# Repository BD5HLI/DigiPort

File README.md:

# 简介

面向八重洲FT-891的FT8模式集成接口，内置一个2口的USB2.0 HUB和一个USB声卡，通过一个Type-C接口连接电脑或者手机，解决FT-891没有内置声卡的问题。

本项目采用了Digirig-Mobile项目（https://github.com/softcomplex/Digirig-Mobile ）的符号库、封装库和3D器件模型，参考了Digirig DR-891的原理图（https://digirig.net/digirig-dr-891-setup-manual/ ）设计，精简了几乎用不到的CM108B GPIO脚的PTT功能，保留了VOX-PTT功能。此外，本项目的被动器件（电阻、电容）均采用0402手焊封装，便于手工焊接。

本项目虽然面向FT-891设计，实际上可以仅使用USB声卡的功能，从而适用于绝大多数带有音频输入输出接口的电台，比如K5、K6手台，配合相应的软件可以实现SSTV、APRS等玩法。

# 电路板渲染图

电路板正面：

电路板反面：

# 接口

DigiPort在电脑侧的接口为type c接口，可使用c to a或c to c数据线连接电脑或者手机；在电台侧的接口包括两个3.5mm的4芯TRRS接口，面向电路板器件面、type c接口在右侧时，左上的TRRS接口为音频/PTT接口，左下的TRRS接口为USB接口。

DigiPort的音频/PTT接口定义如下：  

```
   /\  
  |  |---------> 尖端   RIG_AFOUT 电台音频输出，接FT-891 DATA口的DATA OUT脚  
  |--|  
  |  |---------> 第一环 RIG_AFIN  电台音频输入，接FT-891 DATA口的DATA IN脚  
  |--|  
  |  |---------> 第二环 VOX_PTT   声控PTT，接FT-891 DATA口的PTT脚  
  |--|  
  |  |---------> 底部   GND       信号地，接FT-891 DATA口的GND脚  
__|  |__
|      |  
```

VOX_PTT信号用于没有USB串口的设备控制收发转换，控制源来自CM108B声卡的右声道，推荐采用1kHz或2kHz的单音作为VOX触发信号。

FT-891的DATA**插座**定义如下：

```
    /-----\      1脚：DATA IN  
   / 6 _ 5 \     2脚：GND  
  |4  |_|  3|    3脚：PTT  
   \ 2   1 /     4脚：SHIFT  
    \-----/      5脚：DATA OUT   
                 6脚：SQL   
```

DigiPort的电台侧USB接口定义如下：  

```
   /\  
  |  |---------> 尖端   +5V 电台USB口的+5V电源脚  
  |--|  
  |  |---------> 第一环 D-  电台USB口的D-脚  
  |--|  
  |  |---------> 第二环 D+  电台USB口的D+脚  
  |--|  
  |  |---------> 底部   GND 电台USB口的GND脚  
__|  |__  
|      |  
```

USB Type-B**插头**定义如下：

```
   /-+=+--+=+-\     1脚：+5V     
  /  |=|  |=|  \        
  |   1    2   |    2脚：D-  
  |            |   
  |   4    3   |    3脚：D+  
  |  |=|  |=|  |   
  |--+=+--+=+--|    4脚：GND  
```

# 各目录内容说明

- digiport-891目录下是kicad格式的原理图和PCB图。  
- endboard目录下是采用25mm * 25mm * 40mm对扣小铝壳的端板3D图纸。  
- 3D-models目录下是部分器件的3D模型，来自Digirig-Mobile项目。  
- footprints.pretty目录下是部分器件的封装库，来自Digirig-Mobile项目。  
- symbols目录下是部分器件的符号库，来自Digirig-Mobile项目。  

# 致谢

- 感谢LX6FB提供原版DR-891的照片。

- 感谢BG5ARO对端板设计提出了宝贵建议，并提供了CNC加工。

- 感谢BG5BQB提供了3D打印工艺的端板原型样件。

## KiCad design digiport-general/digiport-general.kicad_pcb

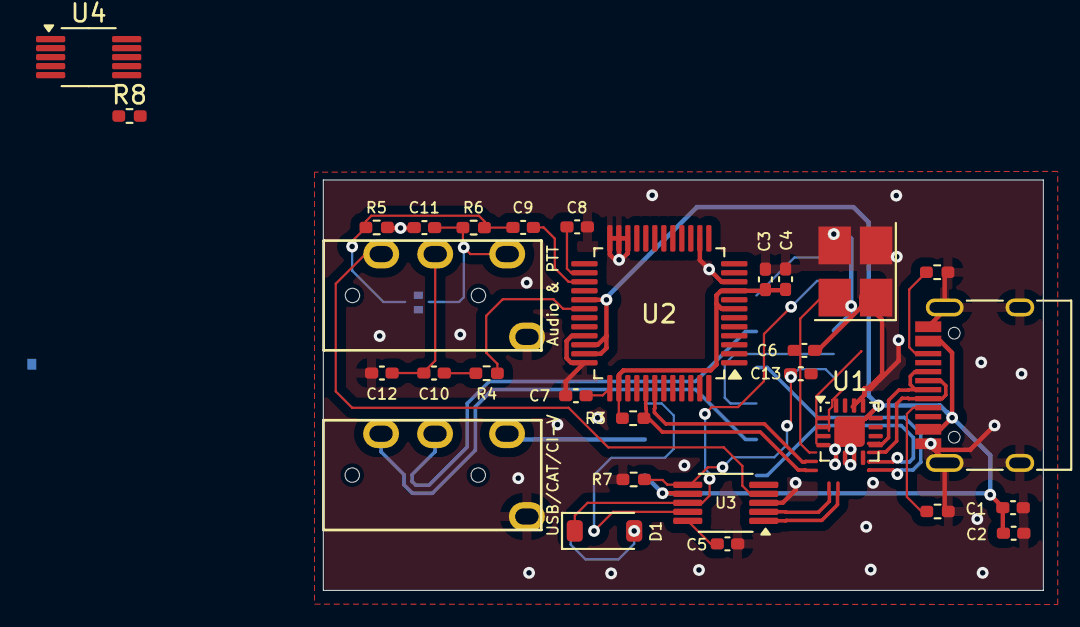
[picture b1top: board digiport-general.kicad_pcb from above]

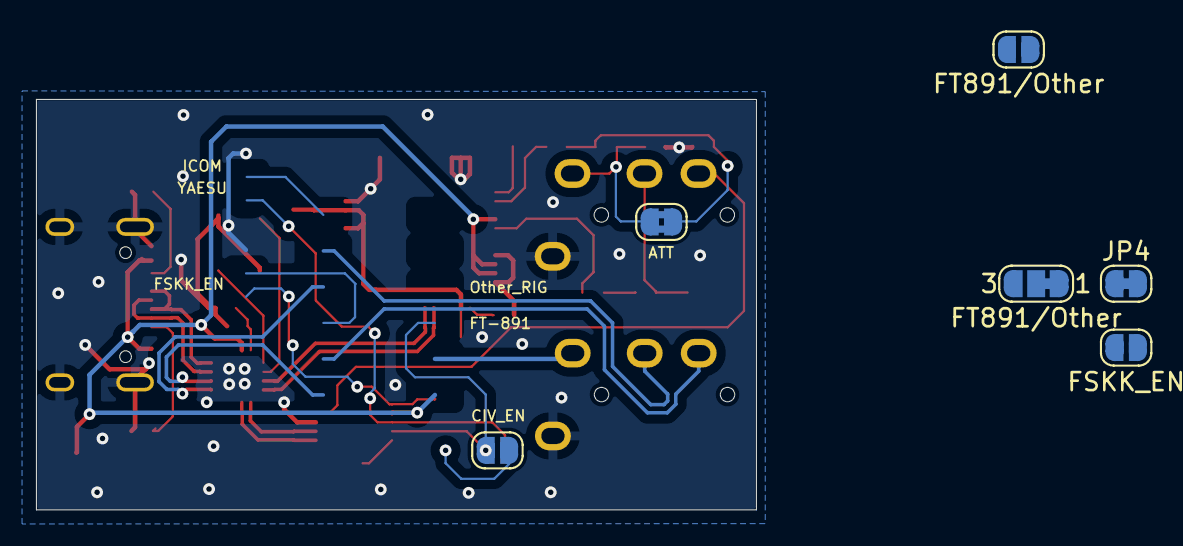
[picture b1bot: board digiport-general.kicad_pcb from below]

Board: 2 copper layers, 40.0 x 22.8 mm, 36 parts (2 on the bottom side), 35 nets.

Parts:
C1, C3, C6, C7, C8, C9, C10: 10uF; C_0402_1005Metric_Pad0.74x0.62mm_HandSolder
C2, C4, C5, C13: 100nF; C_0402_1005Metric_Pad0.74x0.62mm_HandSolder
C11, C12: 1nF; C_0402_1005Metric_Pad0.74x0.62mm_HandSolder
D1: 1N4148W; D_SOD-123
J1: Audio&PTT; TRRS-PJ-320A
J2: USB/CIV/CAT; TRRS-PJ-320A
J3: USB_C_Receptacle_USB2.0_16P; USB_C_Receptacle_HRO_TYPE-C-31-M-12
JP1: FT891/Other; SolderJumper2-BCu
JP2: FT891/Other; SolderJumper3-BCu
JP3: CIV_EN; SolderJumper-2_P1.3mm_Open_RoundedPad1.0x1.5mm
JP4: Yaesu/ICOM; SolderJumper-BCu-Bridged
JP5: FSKK_EN; SolderJumper2-BCu
JP6: ATT; SolderJumper-2_P1.3mm_Bridged2Bar_RoundedPad1.0x1.5mm
R1, R2: 5.1k; R_0402_1005Metric_Pad0.72x0.64mm_HandSolder
R3: 1.5k; R_0402_1005Metric_Pad0.72x0.64mm_HandSolder
R4: 22; R_0402_1005Metric_Pad0.72x0.64mm_HandSolder
R5, R8: 10k; R_0402_1005Metric_Pad0.72x0.64mm_HandSolder
R6: 100k; R_0402_1005Metric_Pad0.72x0.64mm_HandSolder
R7: 4.7k; R_0402_1005Metric_Pad0.72x0.64mm_HandSolder
U1: CH334P; QFN-16-1EP_3x3mm_P0.5mm_EP1.7x1.7mm_ThermalVias
U2: CM108B; LQFP-48_7x7mm_P0.5mm
U3: CH340X; MSOP-10_3x3mm_P0.5mm
U4: CH442E; MSOP-10_3x3mm_P0.5mm
Y1: 12MHz; Crystal_SMD_3225-4Pin_3.2x2.5mm_HandSoldering

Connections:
891USB_D+: U1.6 (DP3+), U4.7 (S2C)
891USB_D-: U1.5 (DM3-), U4.3 (S2B)
+3.3V: C3.1, C4.1, R3.1, U2.7 (PWRSEL), U2.9 (DREG33), U2.38 (MSEL)
+5V: C1.1, C2.1, J3.A4 (VBUS), J3.A9 (VBUS), J3.B4 (VBUS), J3.B9 (VBUS), JP2.1 (A), R8.1, U1.15 (V5), U2.29 (AVDD), U2.34 (AVDD), U2.35 (DVDD), U3.7 (VCC), U4.10 (VCC)
/DU+: J3.A6 (D+), J3.B6 (D+), U1.12 (DPU+)
/DU-: J3.A7 (D-), J3.B7 (D-), U1.11 (DMU-)
/RIG_AFIN: C10.1, C12.1, J1.R1
/RIG_AUOUT: C11.1, J1.T, JP6.2 (B), R6.2
AUDIO_D+: R3.2, U1.4 (DP4+), U2.41 (USBDP)
AUDIO_D-: U1.3 (DM4-), U2.42 (USBDM)
GND: C1.2, C2.2, C3.2, C4.2, C5.2, C6.1, C7.2, C8.1, C11.2, C12.2, C13.1, J1.S, J2.S, J3.A1 (GND), J3.A12 (GND), J3.B1 (GND), J3.B12 (GND), J3.S1 (SHIELD), JP1.1 (A), R1.2, R2.2, R5.1, R7.2, U1.17 (GND), U2.10 (MODE), U2.14 (DVSS), U2.22 (ADSEL), U2.23 (TEST), U2.24 (AVSS), U2.33 (AVSS), U2.36 (DVSS), U3.3 (GND), U4.5 (GND), U4.9 (EN#), Y1.2, Y1.4
unnamed: C10.2, R4.2
unnamed: D1.2 (A), JP3.2 (B)
unnamed: J3.A5 (CC1), R2.1
unnamed: J3.B5 (CC2), R1.1
unnamed: JP1.2 (B), R8.2, U4.1 (IN)
unnamed: C9.1, JP6.1 (A), R5.2, R6.1
unnamed: C6.2, C13.2, U1.16 (VDD33)
unnamed: U1.2 (XI), Y1.3
unnamed: U1.1 (XO), Y1.1
unnamed: C7.1, U2.37 (AREG36)
unnamed: R4.1, U2.30 (LOL)
unnamed: C9.2, U2.27 (MICIN)
unnamed: C8.2, U2.26 (VREF)
unnamed: C5.1, U3.10 (V3)
PC_DTR: JP5.1 (A), R7.1, U3.6 (TNOW/~DTR)
PC_RTS: J1.R2, U3.4 (~RTS)
PC_RxD: JP2.3 (B), JP3.1 (A), U3.9 (RXD)
PC_TxD: D1.1 (K), JP4.1 (A), U3.8 (TXD)
RIGD_R+: J2.R2, U4.6 (DC)
RIGD_R-: J2.R1, U4.4 (DB)
RIGD_T: J2.T, JP2.2 (C)
RIG_RX: JP4.2 (B), U4.2 (S1B)
SERIAL_D+: U1.8 (DP2+), U3.1 (UD+)
SERIAL_D-: U1.7 (DM2-), U3.2 (UD-)

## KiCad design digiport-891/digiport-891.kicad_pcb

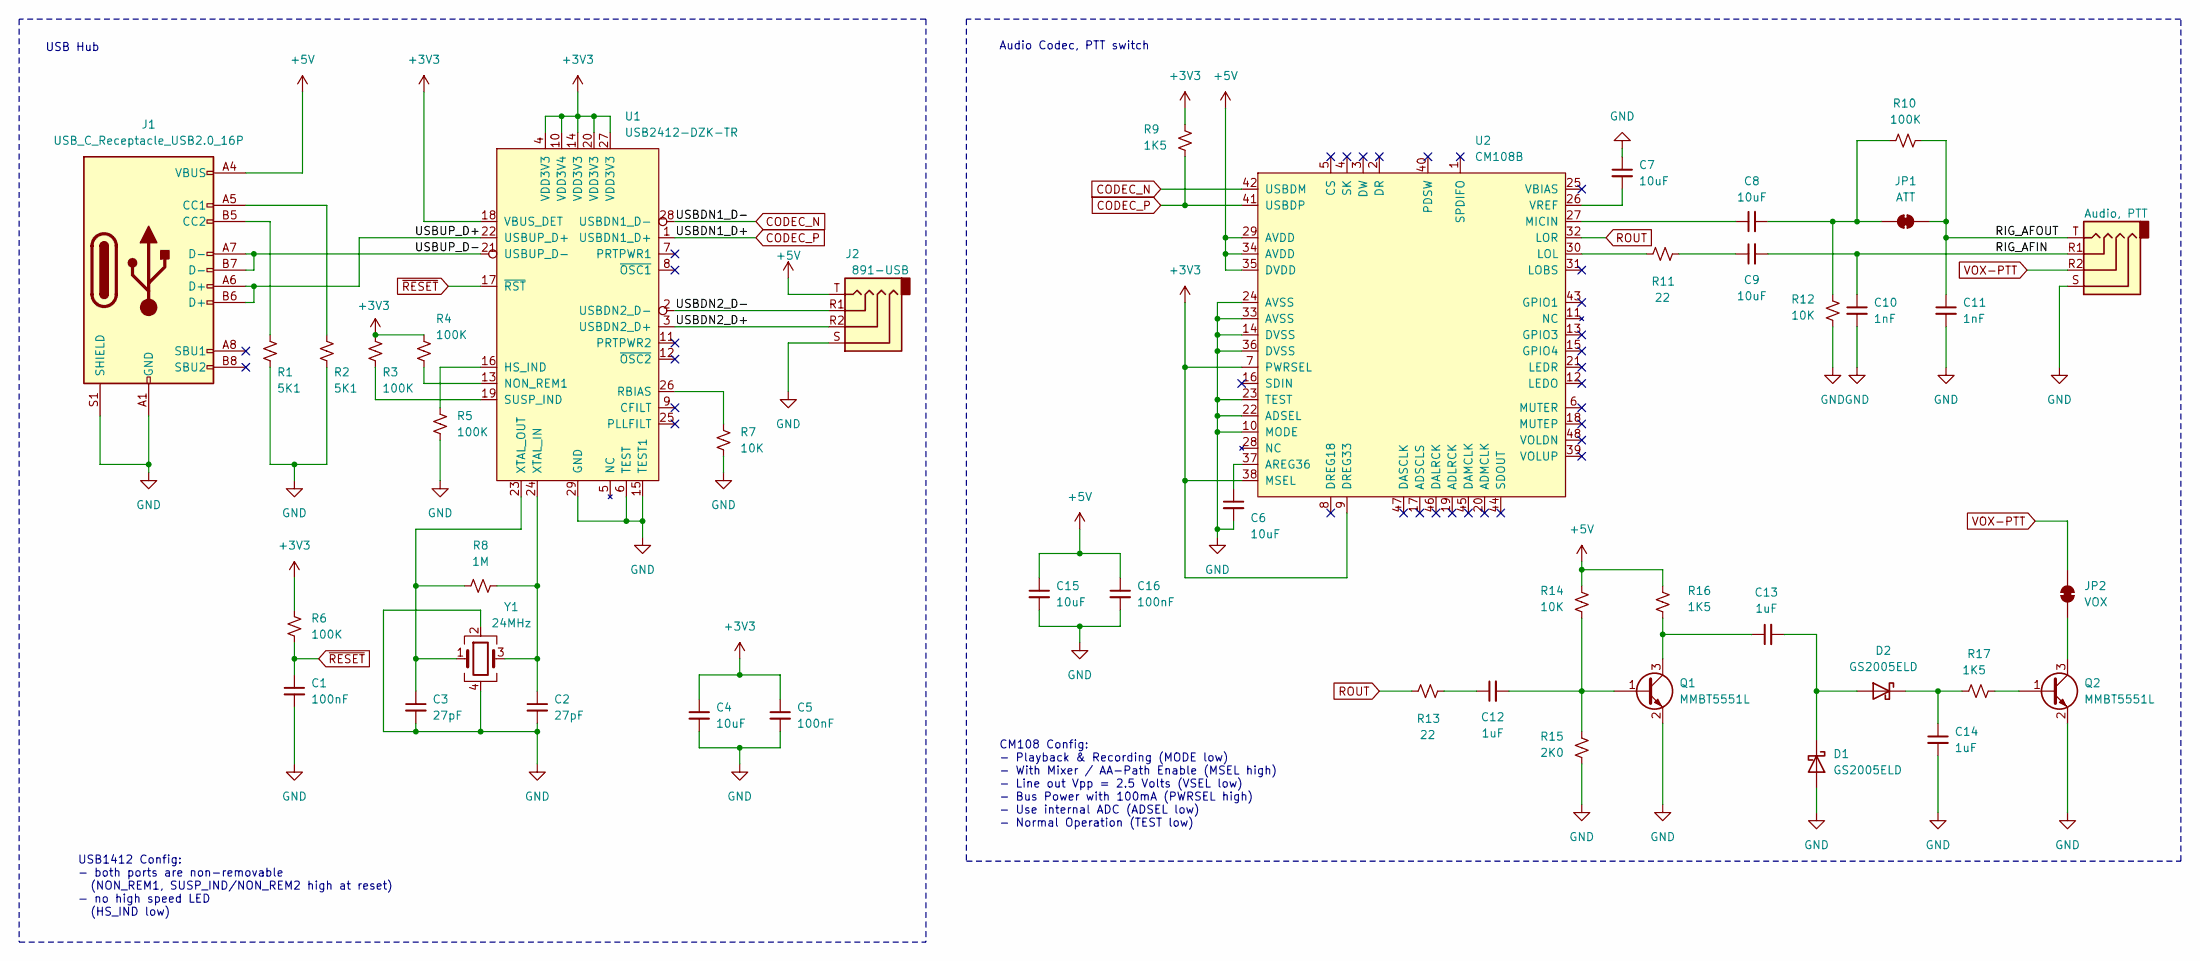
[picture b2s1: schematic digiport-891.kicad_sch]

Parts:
C1, C5, C16: 100nF; C_0402_1005Metric_Pad0.74x0.62mm_HandSolder
C2, C3: 27pF; C_0402_1005Metric_Pad0.74x0.62mm_HandSolder
C4, C6, C7, C8, C9, C15: 10uF; C_0402_1005Metric_Pad0.74x0.62mm_HandSolder
C10, C11: 1nF; C_0402_1005Metric_Pad0.74x0.62mm_HandSolder
C12, C13, C14: 1uF; C_0402_1005Metric_Pad0.74x0.62mm_HandSolder
D1, D2: GS2005ELD; D_SOD-923
J1: USB_C_Receptacle_USB2.0_16P; USB_C_Receptacle_HRO_TYPE-C-31-M-12
J2, J3: PJ-320A; TRRS-PJ-320A
JP1: ATT; SolderJumper-2_P1.3mm_Bridged2Bar_RoundedPad1.0x1.5mm
JP2: VOX; SolderJumper-2_P1.3mm_Bridged2Bar_RoundedPad1.0x1.5mm
Q1, Q2: MMBT5551L; SOT-23
R1, R2: 5K1; C_0402_1005Metric_Pad0.74x0.62mm_HandSolder
R3, R4, R5, R6, R10: 100K; C_0402_1005Metric_Pad0.74x0.62mm_HandSolder
R7, R12, R14: 10K; C_0402_1005Metric_Pad0.74x0.62mm_HandSolder
R8: 1M; C_0402_1005Metric_Pad0.74x0.62mm_HandSolder
R9, R16, R17: 1K5; C_0402_1005Metric_Pad0.74x0.62mm_HandSolder
R11, R13: 22; C_0402_1005Metric_Pad0.74x0.62mm_HandSolder
R15: 2K0; C_0402_1005Metric_Pad0.74x0.62mm_HandSolder
U1: USB2412-DZK-TR; QFN-28-1EP_5x5mm_P0.5mm_EP3.35x3.35mm
U2: CM108B; LQFP-48_7x7mm_P0.5mm
Y1: 24MHz; Crystal_SMD_3225-4Pin_3.2x2.5mm_HandSoldering

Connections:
+3V3: C4.1, C5.1, R3.1, R4.1, R6.1, R9.1, U1.4 (VDD3V3), U1.10 (VDD3V4), U1.14 (VDD3V3), U1.18 (VBUS_DET), U1.20 (VDD3V3), U1.27 (VDD3V3), U2.7 (PWRSEL), U2.9 (DREG33), U2.38 (MSEL)
+5V: C15.1, C16.1, J1.A4 (VBUS), J1.A9 (VBUS), J1.B4 (VBUS), J1.B9 (VBUS), J2.T, R14.1, R16.1, U2.29 (AVDD), U2.34 (AVDD), U2.35 (DVDD)
/RIG_AFIN: C9.2, C10.1, J3.R1
/RIG_AFOUT: C11.1, J3.T, JP1.2 (B), R10.2
/USBDN2_D+: J2.R2, U1.3 (USBDN2_D+)
/USBDN2_D-: J2.R1, U1.2 (USBDN2_D-)
/USBUP_D+: J1.A6 (D+), J1.B6 (D+), U1.22 (USBUP_D+)
/USBUP_D-: J1.A7 (D-), J1.B7 (D-), U1.21 (USBUP_D-)
CODEC_N: U1.28 (USBDN1_D-), U2.42 (USBDM)
CODEC_P: R9.2, U1.1 (USBDN1_D+), U2.41 (USBDP)
GND: C1.2, C2.2, C3.2, C4.2, C5.2, C6.2, C7.1, C10.2, C11.2, C14.2, C15.2, C16.2, D1.2 (A), J1.A1 (GND), J1.A12 (GND), J1.B1 (GND), J1.B12 (GND), J1.S1 (SHIELD), J2.S, J3.S, Q1.2 (E), Q2.2 (E), R1.2, R2.2, R5.2, R7.2, R12.2, R15.2, U1.6 (TEST), U1.15 (TEST1), U1.29 (GND), U2.10 (MODE), U2.14 (DVSS), U2.22 (ADSEL), U2.23 (TEST), U2.24 (AVSS), U2.33 (AVSS), U2.36 (DVSS), Y1.2, Y1.4
unnamed: C9.1, R11.2
unnamed: C12.1, R13.2
unnamed: C13.2, D1.1 (K), D2.2 (A)
unnamed: C14.1, D2.1 (K), R17.1
unnamed: J1.A5 (CC1), R2.1
unnamed: J1.B5 (CC2), R1.1
unnamed: C8.2, JP1.1 (A), R10.1, R12.1
unnamed: JP2.2 (B), Q2.3 (C)
unnamed: C12.2, Q1.1 (B), R14.2, R15.1
unnamed: C13.1, Q1.3 (C), R16.2
unnamed: Q2.1 (B), R17.2
unnamed: R5.1, U1.16 (HS_IND)
unnamed: R4.2, U1.13 (NON_REM1)
unnamed: R7.1, U1.26 (RBIAS)
unnamed: R3.2, U1.19 (SUSP_IND)
unnamed: C2.1, R8.1, U1.24 (XTAL_IN), Y1.3
unnamed: C3.1, R8.2, U1.23 (XTAL_OUT), Y1.1
unnamed: C6.1, U2.37 (AREG36)
unnamed: R11.1, U2.30 (LOL)
unnamed: C8.1, U2.27 (MICIN)
unnamed: C7.2, U2.26 (VREF)
ROUT: R13.1, U2.32 (LOR)
VOX-PTT: J3.R2, JP2.1 (A)
~RESET: C1.1, R6.2, U1.17 (~RST)

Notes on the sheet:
USB Hub
Audio Codec, PTT switch
CM108 Config: - Playback & Recording (MODE low) - With Mixer / AA-Path Enable (MSEL high) - Line out Vpp = 2.5 Volts (VSEL low) - Bus Power with 100mA (PWRSEL high) - Use internal ADC (ADSEL low) - Normal Operation (TEST low)
USB1412 Config: - both ports are non-removable (NON_REM1, SUSP_IND/NON_REM2 high at reset) - no high speed LED (HS_IND low)

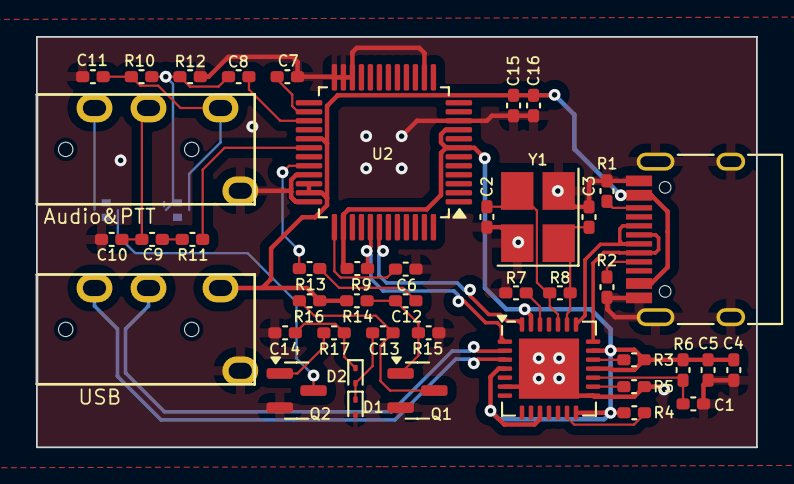
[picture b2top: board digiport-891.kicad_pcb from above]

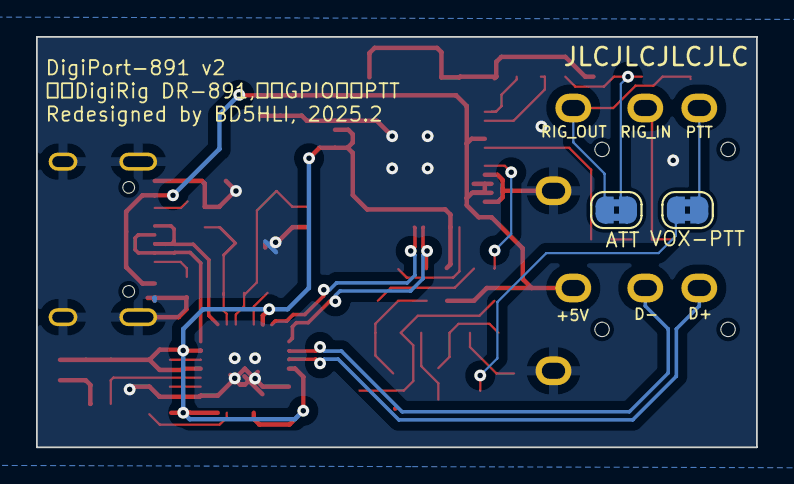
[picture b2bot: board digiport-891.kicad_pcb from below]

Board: 2 copper layers, 40.0 x 22.8 mm, 45 parts (2 on the bottom side), 35 nets.

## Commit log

2025-01-15 增加端板的3D模型STL文件
2025-01-15 renamed digirig-891 to digiport-891
2025-01-15 v2：优化PCB布局，将RIG_AFIN和RIG_AFOUT移动到音频接插件附近，减少过孔数量， 避免焊盘上的过孔。
2025-01-15 Create LICENSE
2025-01-15 优化PCB布线
2025-02-11 add PNG of pcb and PDF of shcematic
    1. PNG of PCB and PDF of schematic are added
    2. Library path is changed to relative path.
2025-03-10 cable pinout file added
2025-03-10 readme updated
2025-04-14 C12 value corrected.
2025-05-23 DigiPort-General version is added
2025-06-29 digiport-gerneral bug fixed, update cable pinout document
2025-10-20 DigiPort-General v2 is added
2025-10-20 Delete digiport-general.pdf
    Delete \digiport-general.pdf
2025-10-20 Delete cable pinout.pdf
    Delete \cable pinout.pdf
2025-10-27 add user manual
2025-10-27 user manual chapter 1 and part of chapter 2
